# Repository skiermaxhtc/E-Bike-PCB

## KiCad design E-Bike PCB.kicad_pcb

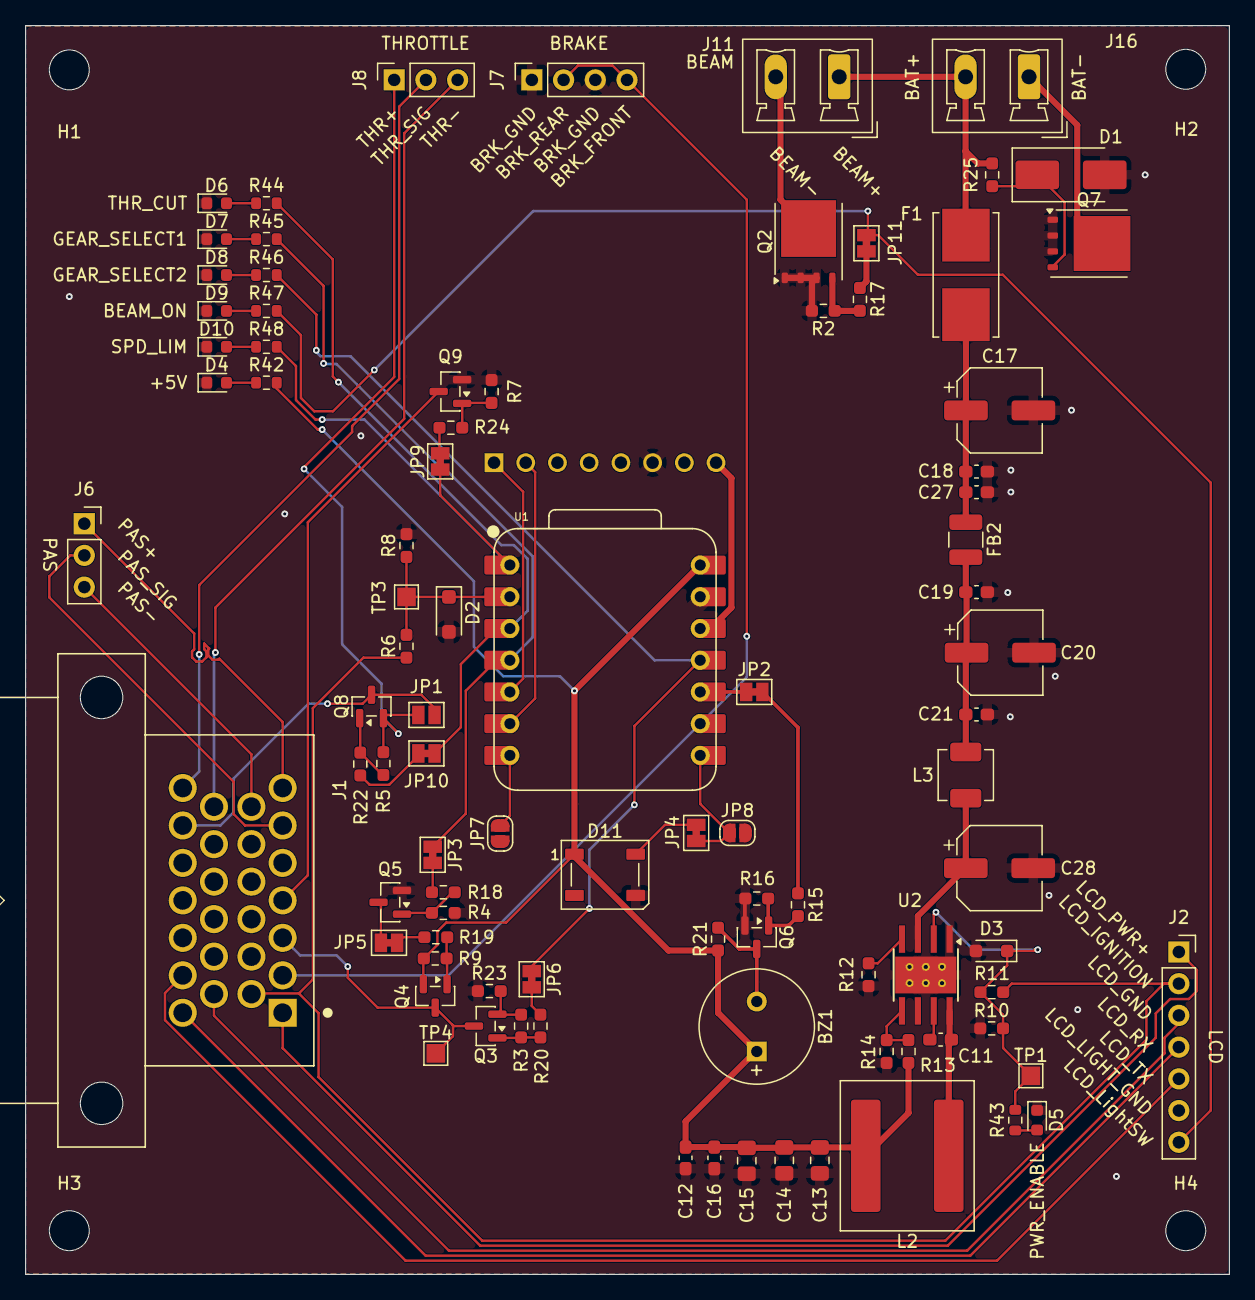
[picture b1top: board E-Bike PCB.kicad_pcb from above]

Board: 6 copper layers, 96.4 x 100.0 mm, 96 parts (1 on the bottom side), 66 nets.

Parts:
BZ1: Buzzer; MagneticBuzzer_PUI_AT-0927-TT-6-R
C11, C16, C18, C21: 100nF; C_0603_1608Metric_Pad1.08x0.95mm_HandSolder
C12, C19, C27: 1nF; C_0603_1608Metric_Pad1.08x0.95mm_HandSolder
C13, C14, C15: 22µF; C_0805_2012Metric_Pad1.18x1.45mm_HandSolder
C17, C20, C28: 4.7µF; CP_Elec_6.3x7.7
D1: SMBJ5371B; D_SMB_Handsoldering
D2: BZT52C3V3; D_SOD-123F
D3: BZT52B5V1S; D_SOD-323_HandSoldering
D4, D5, D6, D7, D8, D9, D10: LED; LED_0603_1608Metric
D11: WS2812B; LED_WS2812B_PLCC4_5.0x5.0mm_P3.2mm
F1: 0154002.DRT; Fuseholder_Littelfuse_Nano2_154x
FB2: FerriteBead; L_1210_3225Metric
H1, H2, H3, H4: MountingHole; MountingHole_3.2mm_M3_ISO7380
J1: 9-6437287-8; TE_9-6437287-8
J2: Conn_01x07_Socket; PinSocket_1x07_P2.54mm_Vertical
J6, J8: Conn_01x03_Socket; PinSocket_1x03_P2.54mm_Vertical
J7: Conn_01x04_Socket; PinSocket_1x04_P2.54mm_Vertical
J11, J16: Conn_01x02_Socket; PhoenixContact_MCV_1,5_2-G-5.08_1x02_P5.08mm_Vertical
JP1: Jumper_2_Open; SolderJumper-2_P1.3mm_Open_Pad1.0x1.5mm
JP2, JP3, JP4, JP5, JP6, JP9, JP10, JP11: SJ_BRG; SolderJumper-2_P1.3mm_Bridged_Pad1.0x1.5mm
JP7, JP8: SLDJP_OPEN; SolderJumper-2_P1.3mm_Open_RoundedPad1.0x1.5mm
L2: 16µH; L_Coilcraft_XAL1060-XXX
L3: 10µH; L_Changjiang_FXL0420
M1: RFID-RC522
Q2, Q7: CSD18534Q5A; TDSON-8-1
Q3, Q5, Q6, Q8, Q9: BSS123; SOT-23
Q4: BSS84; SOT-23
R2, R3, R4, R5, R7, R9, R10, R16: 100k; R_0603_1608Metric_Pad0.98x0.95mm_HandSolder
R6: 180k; R_0603_1608Metric_Pad0.98x0.95mm_HandSolder
R8: 10k; R_0603_1608Metric_Pad0.98x0.95mm_HandSolder
R11: 820k; R_0603_1608Metric_Pad0.98x0.95mm_HandSolder
R12: 64.9k; R_0603_1608Metric_Pad0.98x0.95mm_HandSolder
R13: 115k; R_0603_1608Metric_Pad0.98x0.95mm_HandSolder
R14: 28,7k; R_0603_1608Metric_Pad0.98x0.95mm_HandSolder
R15, R17, R18, R19, R20, R22, R23, R24, R25: 100R; R_0603_1608Metric_Pad0.98x0.95mm_HandSolder
R21: 1k; R_0603_1608Metric_Pad0.98x0.95mm_HandSolder
R42, R43, R44, R45, R46, R47, R48: 330; R_0603_1608Metric
TP1, TP3, TP4: TestPoint; TestPoint_Pad_1.5x1.5mm
U1: XIAO ESP32C6; XIAO-ESP32C6-DIP
U2: LMR38020; Texas_HTSOP-8-1EP_3.9x4.9mm_P1.27mm_EP2.95x4.9mm_Mask2.4x3.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

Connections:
+3.3V: M1.8 (3V3), U1.12 (VCC_3V3)
+5V: BZ1.1 (+), C12.1, C13.1, C14.1, C15.1, C16.1, D11.1 (VDD), L2.2, Q4.2 (S), R9.1, R13.1, R21.1, R42.2, U1.14 (VUSB)
/Project Architecture/POWER - GENERATE/PWR_ENABLE: D3.1 (K), R10.2, R11.2, R43.2, TP1.1 (1_1), U2.2 (EN)
BUZZER: JP2.1 (A), U1.10 (D9)
DEBUG_LED: D11.4 (DIN), JP4.1 (A)
ESP_WakeUp: D2.1 (K), R6.2, R8.1, TP3.1 (1_1), U1.2 (D1)
GND: C12.2, C13.2, C14.2, C15.2, C16.2, C17.2, C18.2, C19.2, C20.2, C21.2, C27.2, C28.2, D1.2 (A), D2.2 (A), D3.2 (A), D4.1 (K), D5.1 (K), D6.1 (K), D7.1 (K), D8.1 (K), D9.1 (K), D10.1 (K), D11.3 (VSS), J7.1, J7.3, M1.6 (GND), Q2.1 (S), Q2.2 (S), Q2.3 (S), Q5.2 (S), Q6.2 (S), Q7.1 (S), Q7.2 (S), Q7.3 (S), Q9.2 (S), R2.2, R4.2, R7.2, R8.2, R10.1, R12.2, R14.2, R16.2, R23.1, U1.13 (GND), U2.1 (PGND), U2.9 (PAD)
GearSelect1: JP3.1 (A), R45.2, U1.4 (D3)
GearSelect2: JP6.1 (A), R46.2, U1.11 (D10)
HighBeam_PWR+: F1.1, J11.1, J16.2, R25.1
HighBeam_PWR-: J11.2, Q2.5 (D)
LCD_GND: J1.14, J2.3
LCD_IGNITION: J1.8, J2.2, R6.1, R11.1
LCD_LightSW: J2.7, JP11.1 (A), R47.2
LCD_PWR+: J1.1, J2.1
LCD_RX: J1.20, J2.4
LCD_TX: J1.21, J2.5
MZ_3Speed: J1.3, Q3.3 (D), Q4.3 (D), TP4.1 (1_1)
MZ_PasSignal: J1.6, J6.2
MZ_Pas_Vcc: J1.7, J6.1
MZ_Pas_Vdd: J1.13, J6.3
MZ_Speed_Limit: J1.4, Q9.3 (D)
MZ_ThrottleSignal: J1.26, J8.2
MZ_Throttle_Vcc: J8.1, JP1.2 (B), Q8.2 (S), R5.2
MZ_Throttle_Vcc-Provide: J1.25, JP1.1 (A), Q8.3 (D)
MZ_Throttle_Vdd: J1.19, J8.3
MZ_~Brake_LOW: J1.2, J7.2, J7.4, U1.9 (D8)
unnamed: BZ1.2 (-), Q6.3 (D), R21.2
unnamed: C17.1, C18.1, C27.1, F1.2, FB2.1
unnamed: C19.1, C20.1, C21.1, FB2.2, L3.1
unnamed: D1.1 (K), Q7.4 (G), R25.2
unnamed: D4.2 (A), R42.1
unnamed: D5.2 (A), R43.1
unnamed: D6.2 (A), R44.1
unnamed: D7.2 (A), R45.1
unnamed: D8.2 (A), R46.1
unnamed: D9.2 (A), R47.1
unnamed: D10.2 (A), R48.1
unnamed: J16.1, Q7.5 (D)
unnamed: JP2.2 (B), R15.1
unnamed: JP3.2 (B), R18.1
unnamed: JP4.2 (B), JP8.1 (A), U1.8 (D7)
unnamed: JP5.1 (A), Q5.3 (D)
unnamed: JP5.2 (B), R19.1
unnamed: JP6.2 (B), R20.1
unnamed: JP7.2 (B), U1.7 (D6)
unnamed: JP9.2 (B), R24.1
unnamed: JP10.2 (B), R22.1
unnamed: JP11.2 (B), R17.1
unnamed: Q2.4 (G), R2.1, R17.2
unnamed: Q3.1 (G), R3.1, R20.2
unnamed: Q3.2 (S), R3.2, R23.2
unnamed: Q4.1 (G), R9.2, R19.2
unnamed: Q5.1 (G), R4.1, R18.2
unnamed: Q6.1 (G), R15.2, R16.1
unnamed: Q8.1 (G), R5.1, R22.2
unnamed: Q9.1 (G), R7.1, R24.2
unnamed: C11.1, U2.7 (BOOT)
unnamed: R13.2, R14.1, U2.5 (FB)
unnamed: R12.1, U2.4 (RT)
unnamed: C11.2, L2.1, U2.8 (SW)
SCL: M1.2 (SCK), U1.6 (D5)
SDA: M1.1 (SDA), U1.5 (D4)
Speed_Limit: JP9.1 (A), R48.2, U1.1 (D0)
Throttle_Cutoff: JP10.1 (A), R44.2, U1.3 (D2)
Vbat: C28.1, L3.2, U2.3 (VIN)

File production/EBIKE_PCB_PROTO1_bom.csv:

Designator,Footprint,Quantity,Value,LCSC Part #
BZ1,MagneticBuzzer_PUI_AT-0927-TT-6-R,1,Buzzer,C96256
"C11, C16, C18, C21",0603,4,100nF,C15725
"C12, C19, C27",0603,3,1nF,C77438
"C13, C14, C15",0805,3,22µF,C29277
"C17, C20, C28",CP_Elec_6.3x7.7,3,4.7µF,C970653
D1,D_SMB_Handsoldering,1,SMBJ5371B,
"D10, D4, D5, D6, D7, D8, D9",0603,7,LED,C2286
D11,LED_WS2812B_PLCC4_5.0x5.0mm_P3.2mm,1,WS2812B,
D2,D_SOD-123F,1,BZT52C3V3,C2112
D3,D_SOD-323_HandSoldering,1,BZT52B5V1S,C78478
F1,Fuseholder_Littelfuse_Nano2_154x,1,0154002.DRT,C206911
FB2,1210,1,FerriteBead,C124094
J1,TE_9-6437287-8,1,9-6437287-8,
"J11, J16","PhoenixContact_MCV_1,5_2-G-5.08_1x02_P5.08mm_Vertical",2,Conn_01x02_Socket,
J2,PinSocket_1x07_P2.54mm_Vertical,1,Conn_01x07_Socket,
"J6, J8",PinSocket_1x03_P2.54mm_Vertical,2,Conn_01x03_Socket,
J7,PinSocket_1x04_P2.54mm_Vertical,1,Conn_01x04_Socket,
JP1,SolderJumper-2_P1.3mm_Open_Pad1.0x1.5mm,1,Jumper_2_Open,
L2,L_Coilcraft_XAL1060-XXX,1,16µH,C108291
L3,L_Changjiang_FXL0420,1,10µH,C108291
M1,RFID-RC522,1,~,RFID-RC522
"Q2, Q7",TDSON-8-1,2,CSD18534Q5A,C115943
"Q3, Q5, Q6, Q8, Q9",SOT-23,5,BSS123,C8491
Q4,SOT-23,1,BSS84,C8492
"R10, R16, R2, R3, R4, R5, R7, R9",0603,8,100k,C25803
R11,0603,1,820k,C23252
R12,0603,1,64.9k,C14891
R13,0603,1,115k,C22783
R14,0603,1,"28,7k",C22928
"R15, R17, R18, R19, R20, R22, R23, R24, R25",0603,9,100R,C22775
R21,0603,1,1k,C21190
"R42, R43, R44, R45, R46, R47, R48",0603,7,330,C23138
R6,0603,1,180k,C22807
R8,0603,1,10k,C25804
"TP1, TP3, TP4",TestPoint_Pad_1.5x1.5mm,3,TestPoint,
U1,XIAO-ESP32C6-DIP,1,XIAO ESP32C6,
U2,Texas_HTSOP-8-1EP_3.9x4.9mm_P1.27mm_EP2.95x4.9mm_Mask2.4x3.1mm_ThermalVias,1,LMR38020,C3192337

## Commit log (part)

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2026-06-14 [CREATE] Initial Commit
2026-06-14 [Schematics] Merging changes from the initial project to the Template
2026-06-20 [SCHEMATICS] Ajout de convertisseur + autres
